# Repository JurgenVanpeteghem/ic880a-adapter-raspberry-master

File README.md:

# ic880a-adapter-raspberry-master

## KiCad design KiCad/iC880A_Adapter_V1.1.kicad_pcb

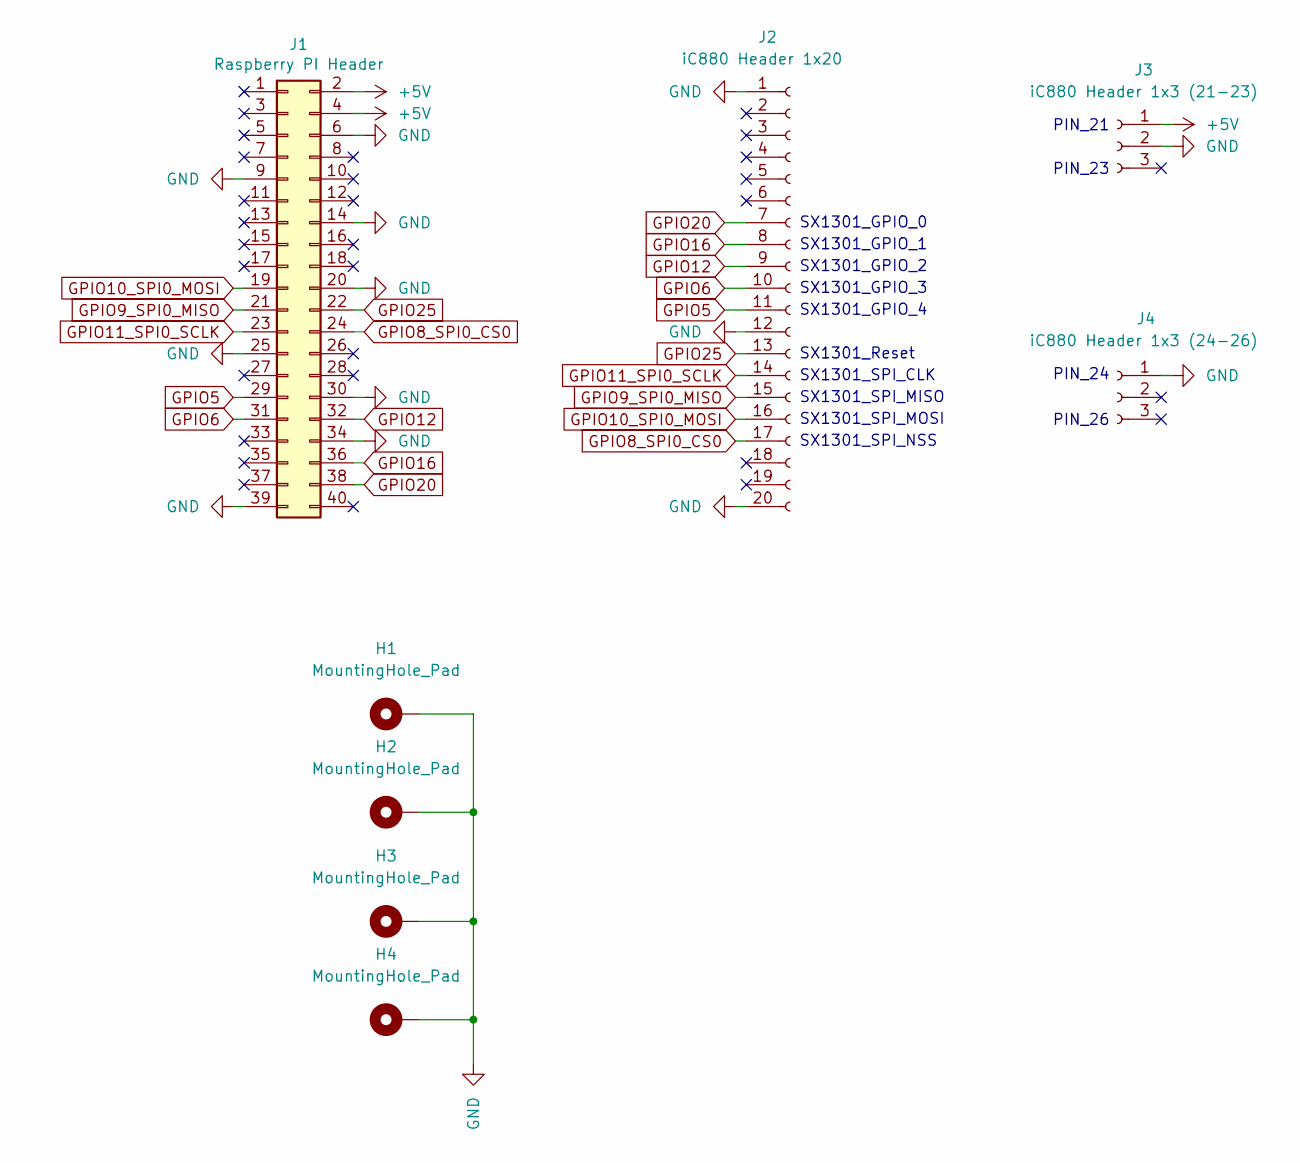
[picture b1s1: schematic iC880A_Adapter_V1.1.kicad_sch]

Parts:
H1, H2, H3, H4: MountingHole_Pad; MountingHole_3.2mm_M3_ISO7380_Pad
J1: Raspberry PI Header; PinSocket_2x20_P2.54mm_Vertical
J2: iC880 Header 1x20; PinSocket_1x20_P2.54mm_Vertical
J3: iC880 Header 1x3 (21-23); PinSocket_1x03_P2.54mm_Vertical
J4: iC880 Header 1x3 (24-26); PinSocket_1x03_P2.54mm_Vertical

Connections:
+5V: J1.2, J1.4, J3.1
GND: H1.1, H2.1, H3.1, H4.1, J1.6, J1.9, J1.14, J1.20, J1.25, J1.30, J1.34, J1.39, J2.1, J2.12, J2.20, J3.2, J4.1
GPIO5: J1.29, J2.11
GPIO6: J1.31, J2.10
GPIO8_SPI0_CS0: J1.24, J2.17
GPIO9_SPI0_MISO: J1.21, J2.15
GPIO10_SPI0_MOSI: J1.19, J2.16
GPIO11_SPI0_SCLK: J1.23, J2.14
GPIO12: J1.32, J2.9
GPIO16: J1.36, J2.8
GPIO20: J1.38, J2.7
GPIO25: J1.22, J2.13

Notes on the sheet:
PIN_24
SX1301_GPIO_2
SX1301_GPIO_4
SX1301_SPI_CLK
SX1301_SPI_MISO
PIN_21
SX1301_GPIO_0
SX1301_GPIO_3
PIN_23
PIN_26
SX1301_SPI_MOSI
SX1301_Reset
SX1301_SPI_NSS
SX1301_GPIO_1

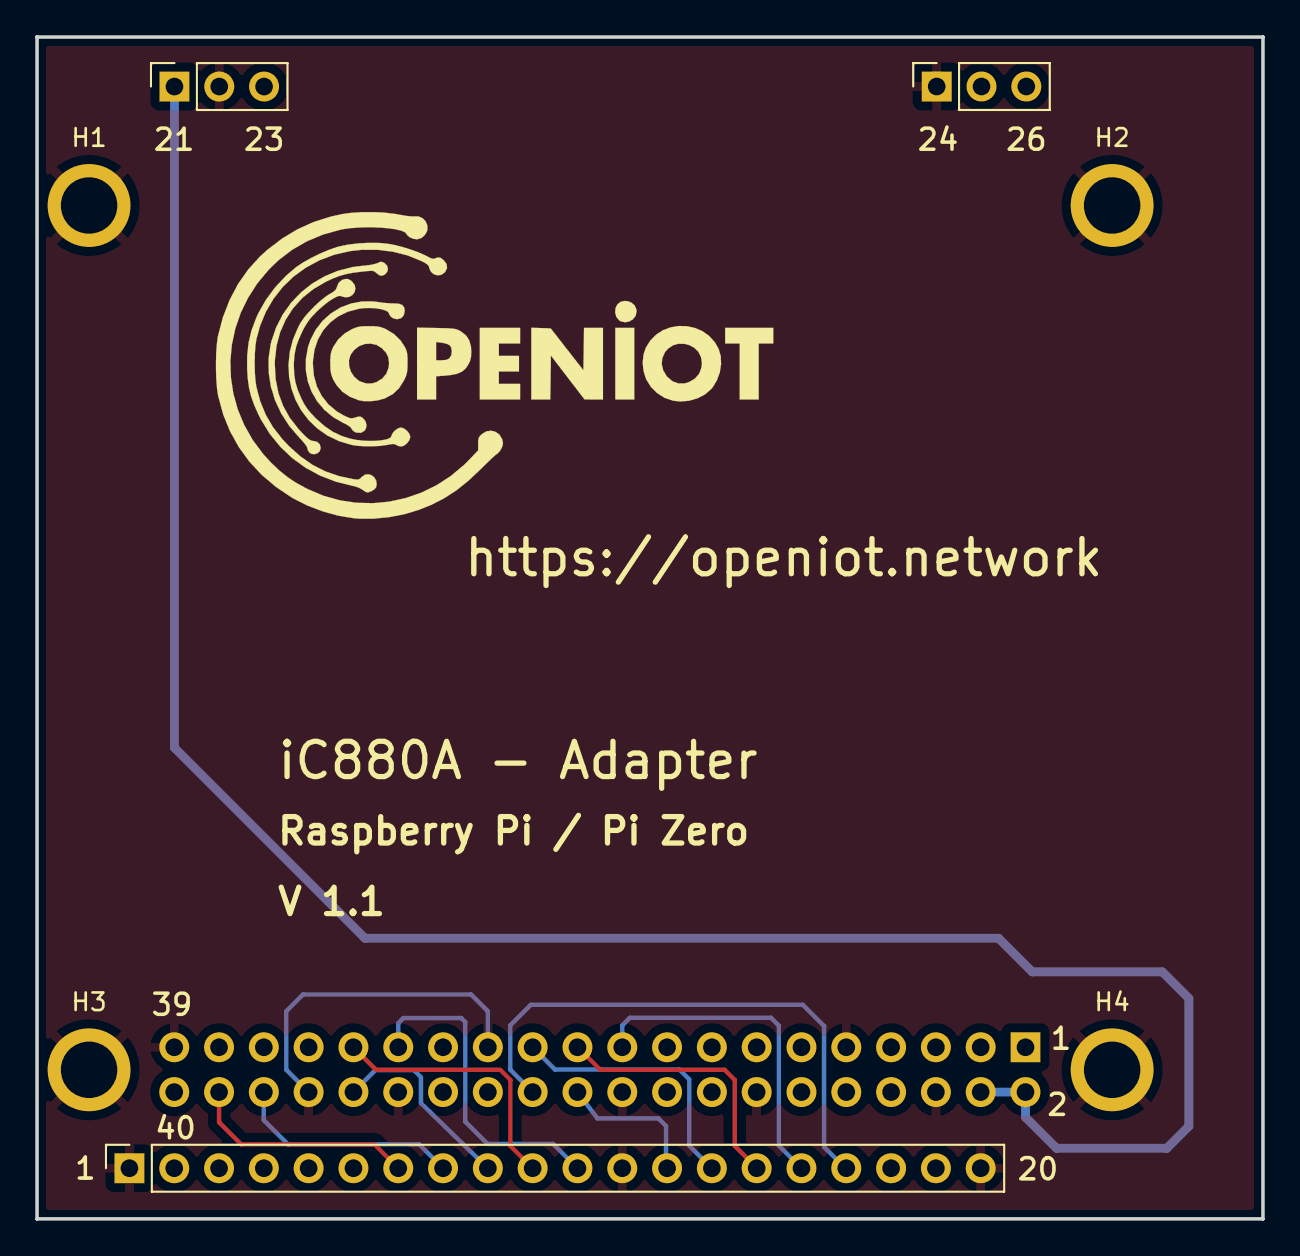
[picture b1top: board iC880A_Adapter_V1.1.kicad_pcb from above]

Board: 2 copper layers, 69.5 x 67.0 mm, 8 parts (1 on the bottom side), 12 nets.
